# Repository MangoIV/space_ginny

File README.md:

# space_ginny
## What is this?
This is basically a ginny clone. Ginny is a hackable asetniop input device by Germ distributed on gboards.ca with closed source hardware and open source software.

## Who is this for?
This is for all the people who can't afford shipping from canada or want an OLED or a custom pcb colour on their ginny. 
This is also for all the people who like a more aggressive row stagger.
Furthermore it is for all the people who don't want to solder more than they need to. 

## What is the current state of the project?
The first PCBs have been ordered and are soldered and running QMK. Although there is no complete firmware yet, it is therefore proven that the hardware is able to be run as asetniop input device.
The next step is to create a working asetniop firmware. 

## What do you need to build a space_ginny?
The PCBs are reversible. You will need two of those. You will also need 2 pro micros or equivalents like the elite-c. Additionally you'll need 2 trrs jacks and 10 mx/choc switches and caps. 
2 reset buttons are not necessary but it will be more convenient for you to reset the board. The OLEDs aren't necessary either and you of course can leave them out if you want to go wireless or don't like them.

## How would you build them
Put headers in the outlined rectangles on the pro micro footprints. Solder them. Solder switches on same side. Solder TRRS jacks. Solder OLEDs. Bridge the jumpers on the top side. Solder the reset switch on the top side. Solder the switches. 
Repeat this whole procedure for the other pcb, this time on the backside.

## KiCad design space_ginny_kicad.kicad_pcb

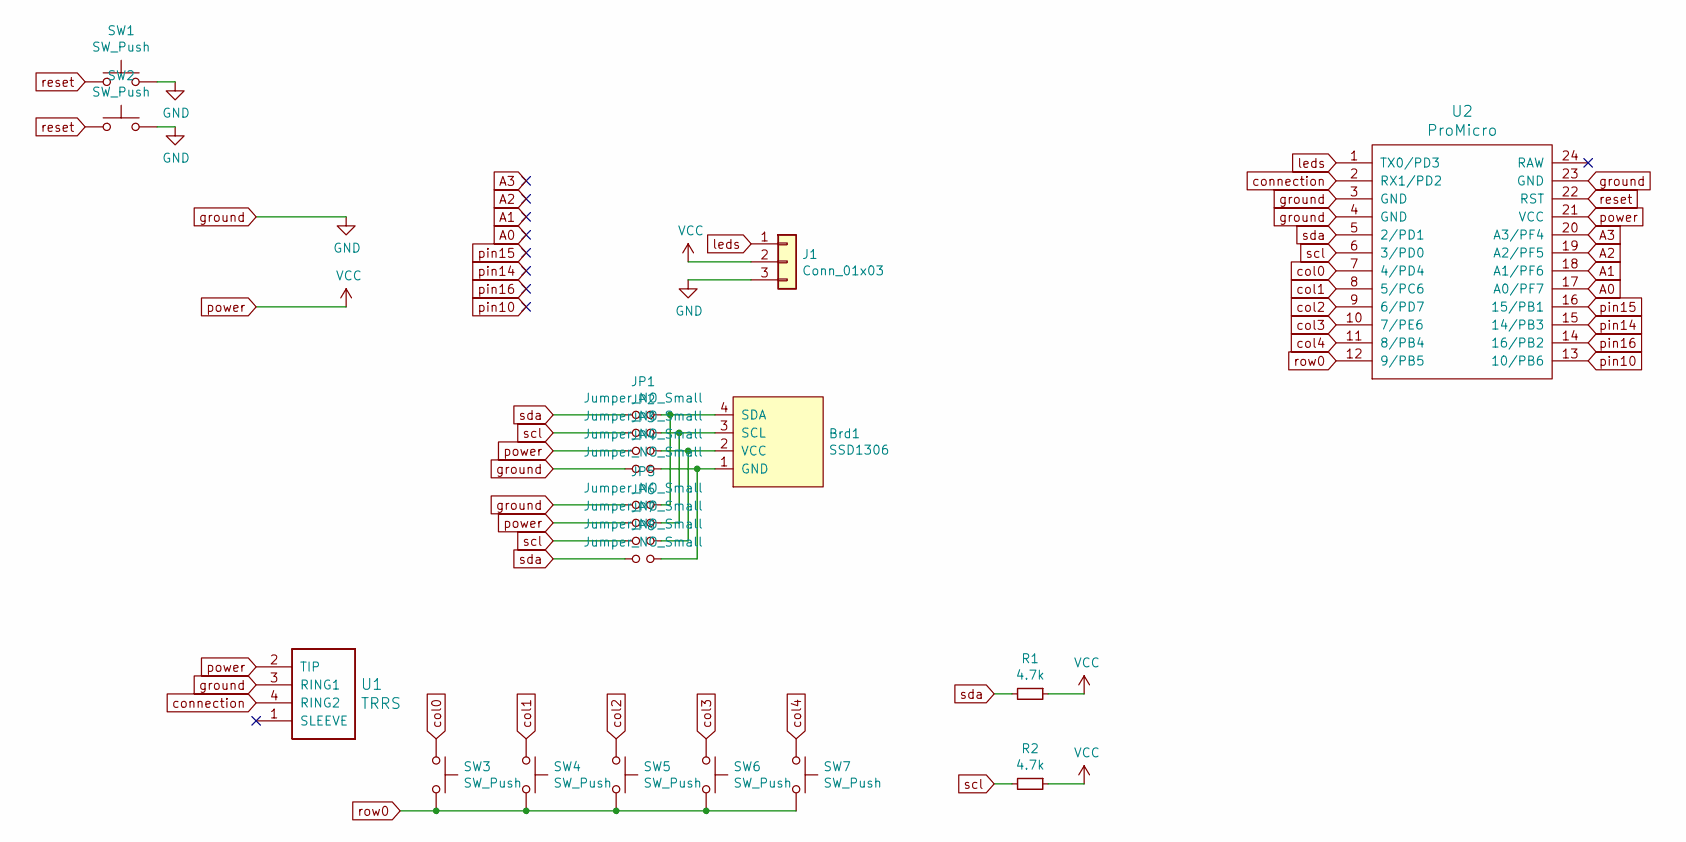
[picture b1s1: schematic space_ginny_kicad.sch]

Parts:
Brd1: SSD1306; 128x64OLED
J1: Conn_01x03; PinSocket_1x03_P2.00mm_Vertical
JP1, JP2, JP3, JP4, JP5, JP6, JP7, JP8: Jumper_NO_Small; SolderJumper-2_P1.3mm_Open_Pad1.0x1.5mm
R1, R2: 4.7k; R_0805_2012Metric
SW1, SW2: SW_Push; SW_SPST_TL3342
SW3, SW4, SW5, SW6, SW7: SW_Push; CherryMX_Choc_1u_reversible
U1: TRRS; TRRS-PJ-320A-dual
U2: ProMicro

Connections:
A0: U2.17 (A0/PF7)
A1: U2.18 (A1/PF6)
A2: U2.19 (A2/PF5)
A3: U2.20 (A3/PF4)
unnamed: Brd1.1 (GND), JP4.2, JP8.2
unnamed: Brd1.2 (VCC), JP3.2, JP7.2
unnamed: Brd1.3 (SCL), JP2.2, JP6.2
unnamed: Brd1.4 (SDA), JP1.2, JP5.2
col0: SW3.1, U2.7 (4/PD4)
col1: SW4.1, U2.8 (5/PC6)
col2: SW5.1, U2.9 (6/PD7)
col3: SW6.1, U2.10 (7/PE6)
col4: SW7.1, U2.11 (8/PB4)
connection: U1.4 (RING2), U2.2 (RX1/PD2)
ground: J1.3, JP4.1, JP5.1, SW1.2, SW2.2, U1.3 (RING1), U2.3 (GND), U2.4 (GND), U2.23 (GND)
leds: J1.1, U2.1 (TX0/PD3)
pin10: U2.13 (10/PB6)
pin14: U2.15 (14/PB3)
pin15: U2.16 (15/PB1)
pin16: U2.14 (16/PB2)
power: J1.2, JP3.1, JP6.1, R1.1, R2.1, U1.2 (TIP), U2.21 (VCC)
reset: SW1.1, SW2.1, U2.22 (RST)
row0: SW3.2, SW4.2, SW5.2, SW6.2, SW7.2, U2.12 (9/PB5)
scl: JP2.1, JP7.1, R2.2, U2.6 (3/PD0)
sda: JP1.1, JP8.1, R1.2, U2.5 (2/PD1)

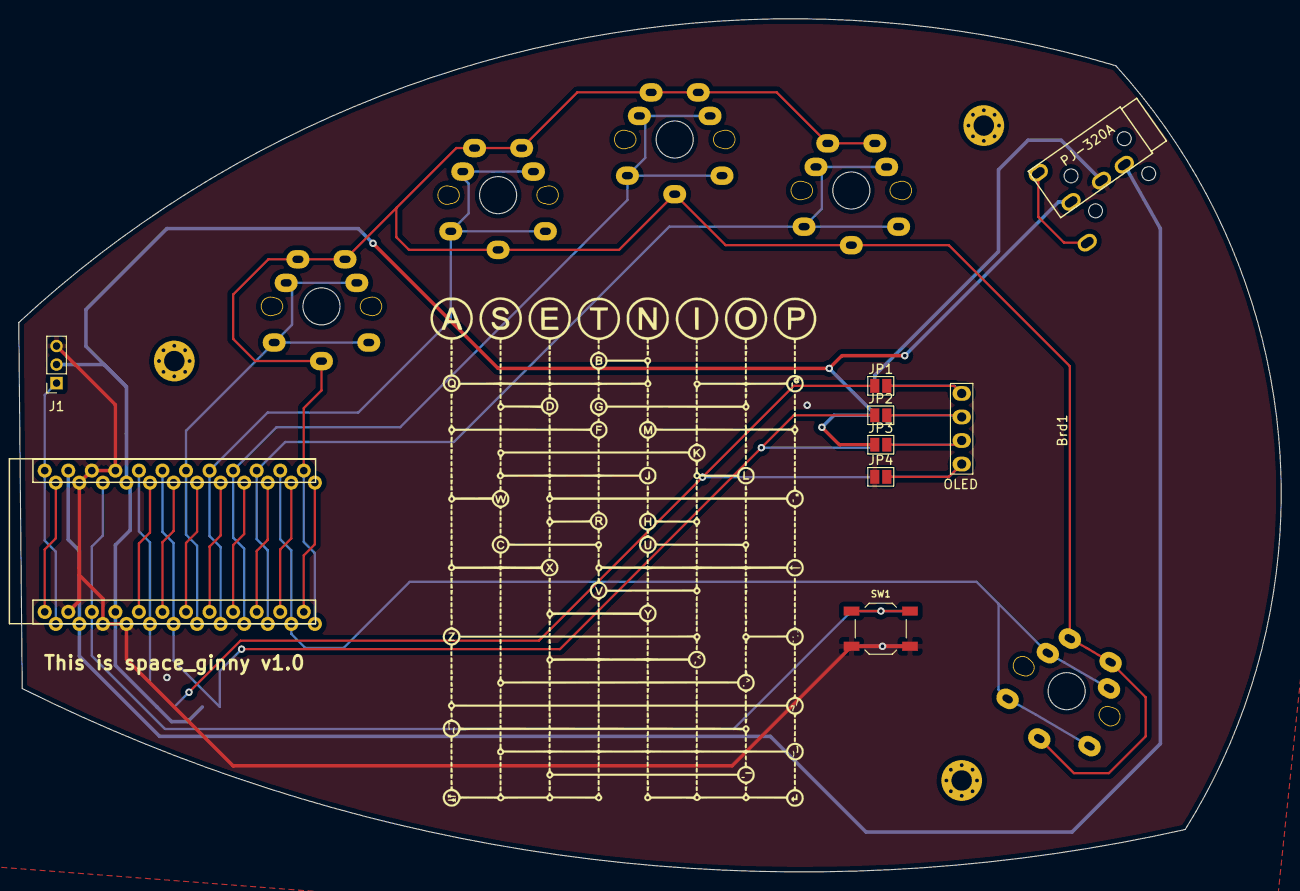
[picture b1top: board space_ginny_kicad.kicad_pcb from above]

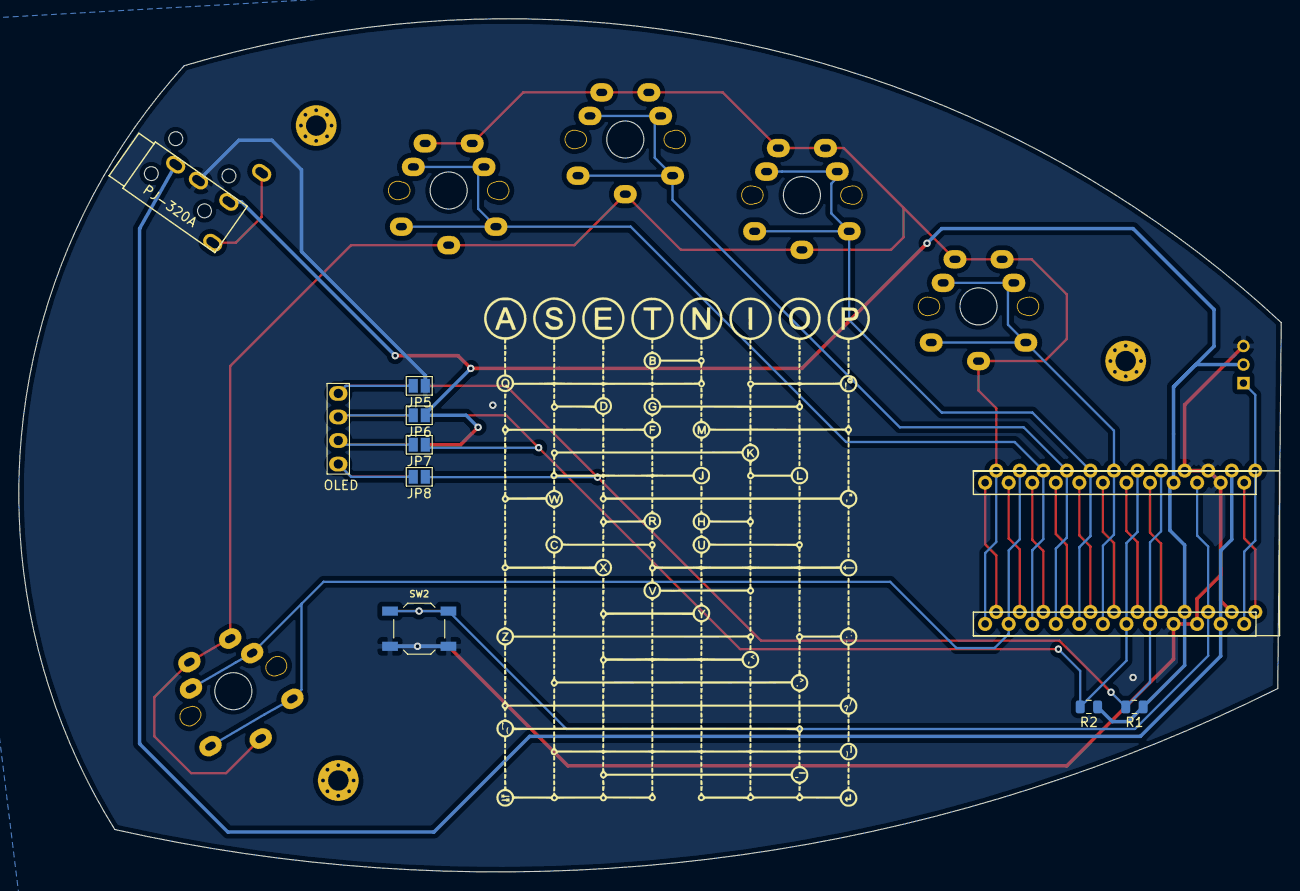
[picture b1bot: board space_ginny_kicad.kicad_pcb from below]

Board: 2 copper layers, 136.2 x 92.0 mm, 24 parts (8 on the bottom side), 17 nets.

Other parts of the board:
 : MountingHole_2.2mm_M2_Pad_Via
 #2,  #3: MountingHole_2.2mm_M2_Pad_Via

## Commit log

2020-10-14 added git submodules and initialised project
2020-10-14 added some footprints to the schematic
2020-10-14 added footpring for ssd 1306 as well as the corresponding symbol
2020-10-14 finished the schematics, so far
2020-10-14 - started the PCB design - finished the schematics (a second time ) - changed the LEDs to ws2812b (per key doesn't make sense with 5 keys)
2020-10-15 arranges, added edgecuts, started routing
2020-10-15 removed the LEDs cause they're useless ans instead added a breakout to add a strip if needed. Finished routing
2020-10-15 added groundfill and exported the outlines in svgs (new folder)
2020-10-15 added silkscreen art, placed some traces new
2020-10-16 changed mounting holes, added backside graphic
2020-10-16 changed filenames, generated gerbers and drill files
2020-10-25 added pictures of the first working space_ginny
